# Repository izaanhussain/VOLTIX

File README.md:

# VOLTIX V1 DC-DC Boost Converter

a DC-DC Boost Converter circuit designed in KiCad which it takes an input voltage of 5V DC and provides a nominally regulated 9V output.

##

## shematics

## PCB 

## Design

| Parameter | Target |
|---|---:|
| Input voltage | 5 V DC |
| Output voltage | 9 V DC |
| Maximum output current | 100 mA |
| Converter IC | MC34063AD |
| PCB | 2-layer |
| Board outline | 41 mm × 29 mm |

## Components

MC34063AD switch mode regulator

120uH Inductor

1N5819 Schottky Diode

Feedback Resistors and Current Sensing Resistor

Input, Output and Timing Capacitors

2-Pin Input and Output Connectors

the list of components can be found in the BOM.csv 

## Project Files

`PCB/VOLTIX.kicad_sch`

KiCad Schematic

`PCB/VOLTIX.kicad_pcb`

KiCad PCB

`PCB/VOLTIX.kicad_pro`

KiCad Project file.

`Production/Gerbers.zip`

Gerbers and Drills/Fabrication.

`journal.md`

Project notes.

`BOM.csv`

Bill of Materials

## Opening Project

Download or Clone the project.

Open `PCB/VOLTIX.kicad_pro`.

From the project manager open the Schematic or PCB.

## Manufacturing

The Gerbers.zip is in the Production folder
## Credits 
ME AND ONLYY MEE 
this project was shipped to #embasyy YSWS by hackclub 
more proejectss comingg Thanks

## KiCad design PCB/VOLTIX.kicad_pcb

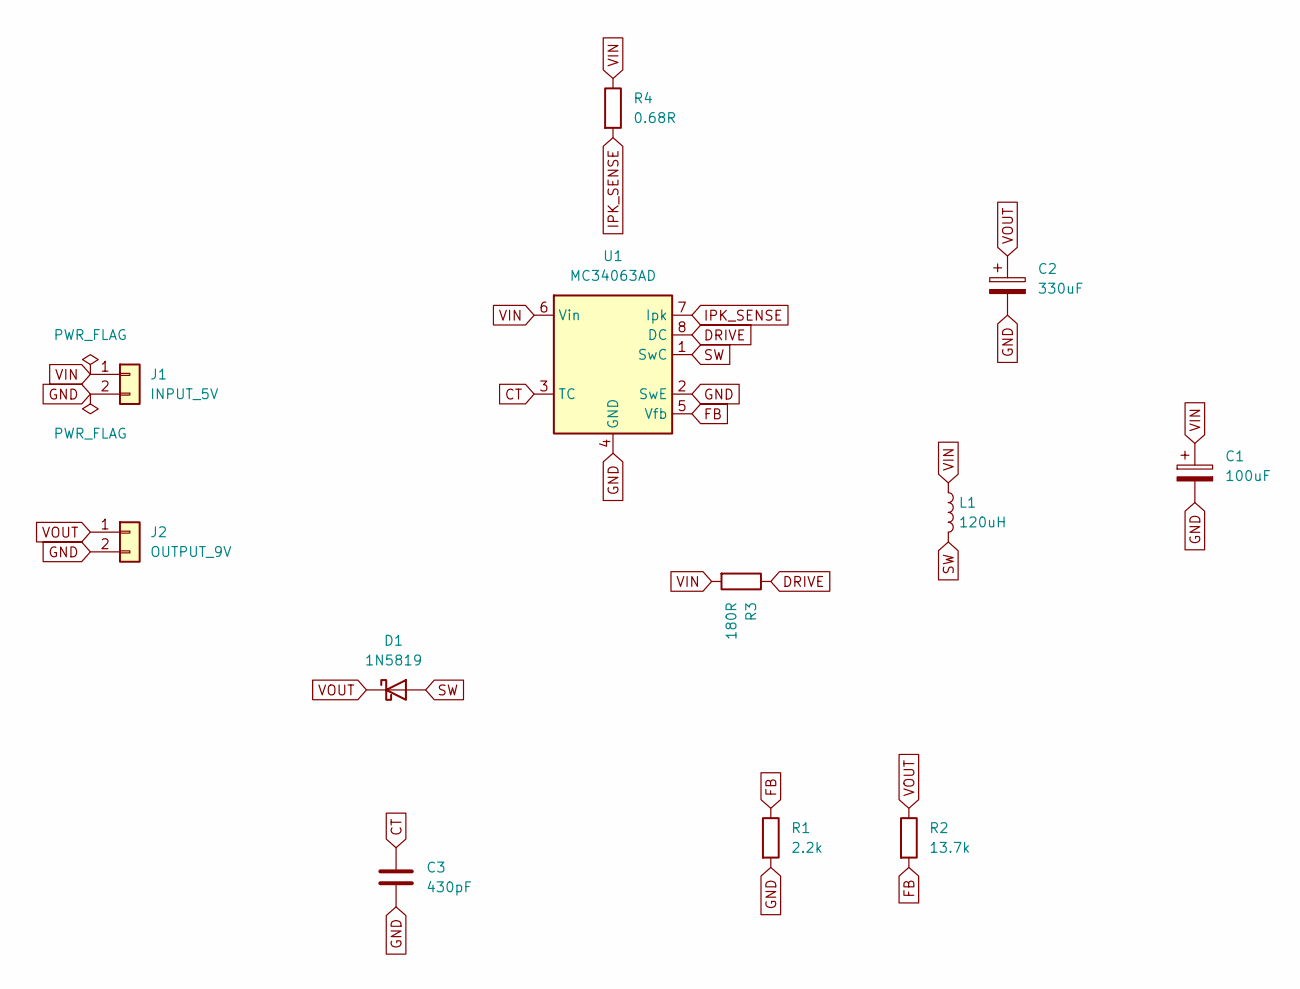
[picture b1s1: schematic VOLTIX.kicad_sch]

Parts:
C1: 100uF; CP_Radial_D8.0mm_P3.50mm
C2: 330uF; CP_Radial_D10.0mm_P5.00mm
C3: 430pF; C_0805_2012Metric
D1: 1N5819; D_DO-41_SOD81_P10.16mm_Horizontal
J1: INPUT_5V; PinHeader_1x02_P2.54mm_Vertical
J2: OUTPUT_9V; PinHeader_1x02_P2.54mm_Vertical
L1: 120uH; L_12x12mm_H8mm
R1: 2.2k; R_0805_2012Metric
R2: 13.7k; R_0805_2012Metric
R3: 180R; R_1206_3216Metric
R4: 0.68R; R_2512_6332Metric
U1: MC34063AD; SOIC-8_3.9x4.9mm_P1.27mm

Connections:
CT: C3.1, U1.3 (TC)
DRIVE: R3.1, U1.8 (DC)
FB: R1.1, R2.2, U1.5 (Vfb)
GND: C1.2, C2.2, C3.2, J1.2, J2.2, R1.2, U1.2 (SwE), U1.4 (GND)
IPK_SENSE: R4.2, U1.7 (Ipk)
SW: D1.2 (A), L1.2, U1.1 (SwC)
VIN: C1.1, J1.1, L1.1, R3.2, R4.1, U1.6 (Vin)
VOUT: C2.1, D1.1 (K), J2.1, R2.1

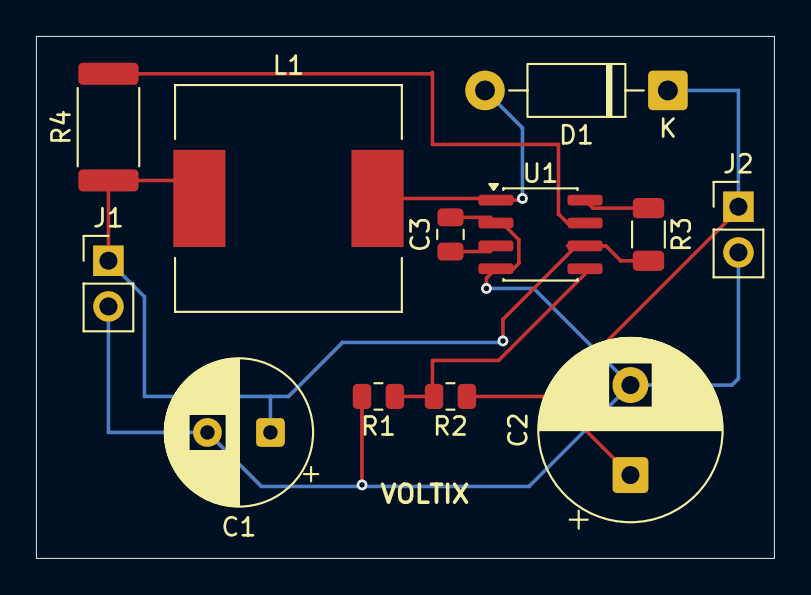
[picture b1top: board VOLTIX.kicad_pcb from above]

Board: 2 copper layers, 41.0 x 29.0 mm, 12 parts (0 on the bottom side), 8 nets.

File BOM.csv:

Reference,Quantity,Value,Footprint,Description
U1,1,MC34063AD,Package_SO:SOIC-8_3.9x4.9mm_P1.27mm,DC-DC switching regulator
L1,1,120uH,Inductor_SMD:L_12x12mm_H8mm,Power inductor
D1,1,1N5819,Diode_THT:D_DO-41_SOD81_P10.16mm_Horizontal,Schottky diode
R1,1,2.2k,Resistor_SMD:R_0805_2012Metric,Feedback resistor
R2,1,13.7k,Resistor_SMD:R_0805_2012Metric,Feedback resistor
R3,1,180R,Resistor_SMD:R_1206_3216Metric,Driver resistor
R4,1,0.68R,Resistor_SMD:R_2512_6332Metric,Current-sense resistor
C1,1,100uF,Capacitor_THT:CP_Radial_D8.0mm_P3.50mm,Input capacitor
C2,1,330uF,Capacitor_THT:CP_Radial_D10.0mm_P5.00mm,Output capacitor
C3,1,430pF,Capacitor_SMD:C_0805_2012Metric,Timing capacitor
J1,1,INPUT_5V,Connector_PinHeader_2.54mm:PinHeader_1x02_P2.54mm_Vertical,2-pin input connector
J2,1,OUTPUT_9V,Connector_PinHeader_2.54mm:PinHeader_1x02_P2.54mm_Vertical,2-pin output connector
